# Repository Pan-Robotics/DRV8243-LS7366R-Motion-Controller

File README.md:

# DRV8243-LS7366R-Motion-Controller
Motion Control PCB, integrating the DRV8243 motor driver and LS7366R encoder reader for feedback control of DC motors

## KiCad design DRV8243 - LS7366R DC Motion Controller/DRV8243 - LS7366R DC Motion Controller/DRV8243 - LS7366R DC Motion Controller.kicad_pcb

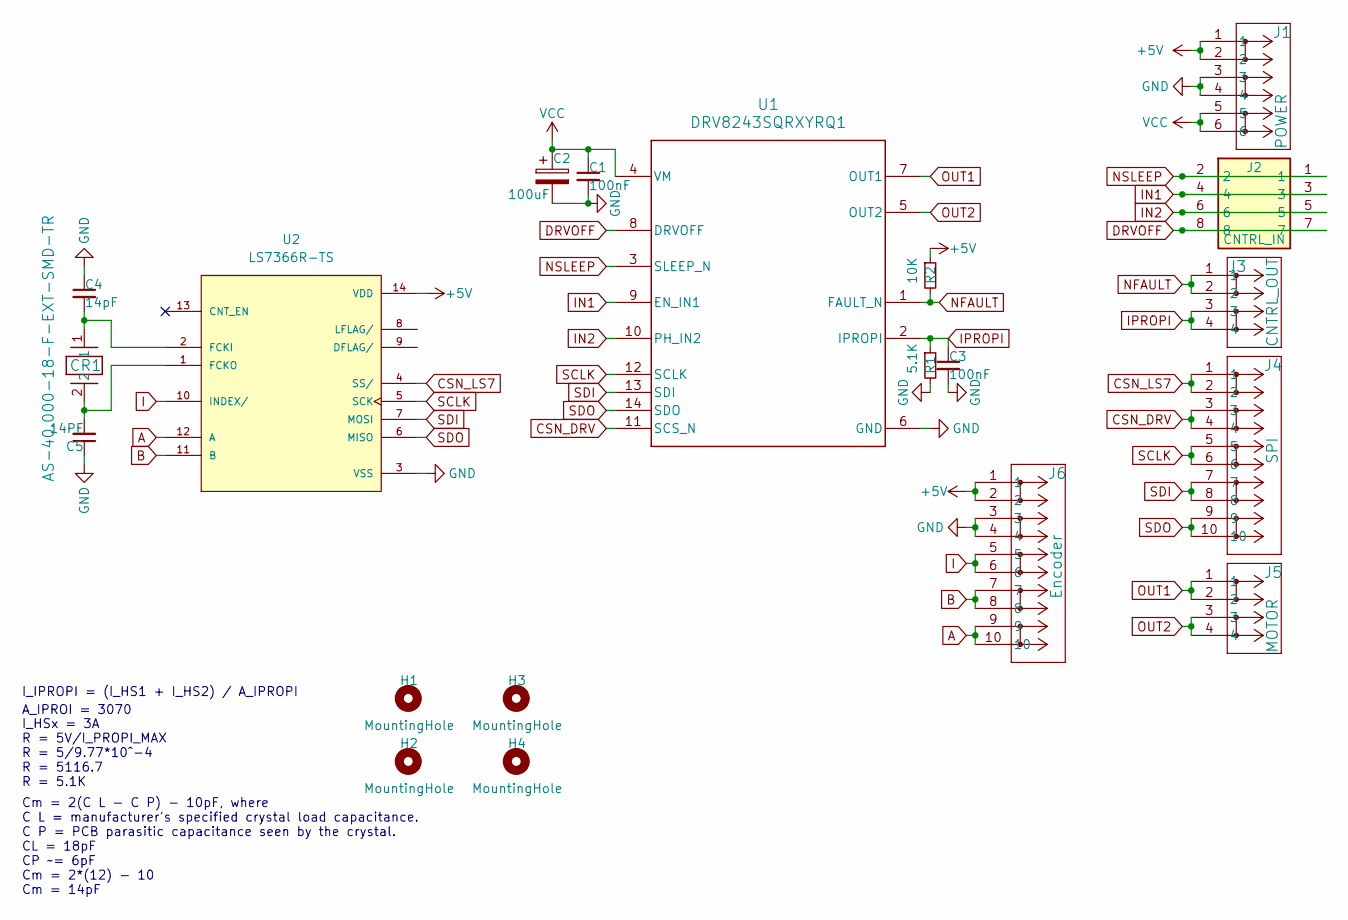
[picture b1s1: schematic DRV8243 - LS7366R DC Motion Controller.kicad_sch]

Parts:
C1, C3: 100nF; C_1206_3216Metric_Pad1.33x1.80mm_HandSolder
C2: 100uF; C_Elec_8x10.2
C4: 14pF; C_1206_3216Metric_Pad1.33x1.80mm_HandSolder
C5: 14PF; C_1206_3216Metric_Pad1.33x1.80mm_HandSolder
CR1: AS-40.000-18-F-EXT-SMD-TR; CRYSTAL_RAMI_HC-49&slash_S_STD_RAM
H1, H2, H3, H4: MountingHole; MountingHole_3.2mm_M3_Pad_Via
J1: POWER; CONN_1862055
J2: CNTRL_IN; 1862068; Mouser Part Number 651-1862068
J3: CNTRL_OUT; CONN_1862042
J4: SPI; CONN_1862071
J5: MOTOR; CONN_1862042
J6: Encoder; CONN_1862071
R1: 5.1K; R_1206_3216Metric_Pad1.30x1.75mm_HandSolder
R2: 10K; R_1206_3216Metric_Pad1.30x1.75mm_HandSolder
U1: DRV8243SQRXYRQ1; RXY0014A-MFG
U2: LS7366R-TS; SOP65P640X120-14N; PARTREV June 2014

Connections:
+5V: J1.1, J1.2, J6.1, J6.2, R2.1, U2.14 (VDD)
A: J6.9, J6.10, U2.12 (A)
B: J6.7, J6.8, U2.11 (B)
CSN_DRV: J4.3, J4.4, U1.11 (SCS_N)
CSN_LS7: J4.1, J4.2, U2.4 (SS/)
DRVOFF: J2.7, J2.8, U1.8 (DRVOFF)
GND: C1.2, C2.2, C3.2, C4.1, C5.1, J1.3, J1.4, J6.3, J6.4, R1.2, U1.6 (GND), U2.3 (VSS)
I: J6.5, J6.6, U2.10 (INDEX/)
IN1: J2.3, J2.4, U1.9 (EN_IN1)
IN2: J2.5, J2.6, U1.10 (PH_IN2)
IPROPI: C3.1, J3.3, J3.4, R1.1, U1.2 (IPROPI)
NFAULT: J3.1, J3.2, R2.2, U1.1 (FAULT_N)
NSLEEP: J2.1, J2.2, U1.3 (SLEEP_N)
unnamed: C4.2, CR1.1, U2.2 (FCKI)
unnamed: C5.2, CR1.2, U2.1 (FCKO)
OUT1: J5.1, J5.2, U1.7 (OUT1)
OUT2: J5.3, J5.4, U1.5 (OUT2)
SCLK: J4.5, J4.6, U1.12 (SCLK), U2.5 (SCK)
SDI: J4.7, J4.8, U1.13 (SDI), U2.7 (MOSI)
SDO: J4.9, J4.10, U1.14 (SDO), U2.6 (MISO)
VCC: C1.1, C2.1, J1.5, J1.6, U1.4 (VM)

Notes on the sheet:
I_HSx = 3A R = 5V/I_PROPI_MAX R = 5/9.77*10^-4 R = 5116.7 R = 5.1K
A_IPROI = 3070
Cm = 2(C L - C P) - 10pF, where C L = manufacturer's specified crystal load capacitance. C P = PCB parasitic capacitance seen by the crystal. CL = 18pF CP ~= 6pF Cm = 2*(12) - 10 Cm = 14pF
I_IPROPI = (I_HS1 + I_HS2) / A_IPROPI

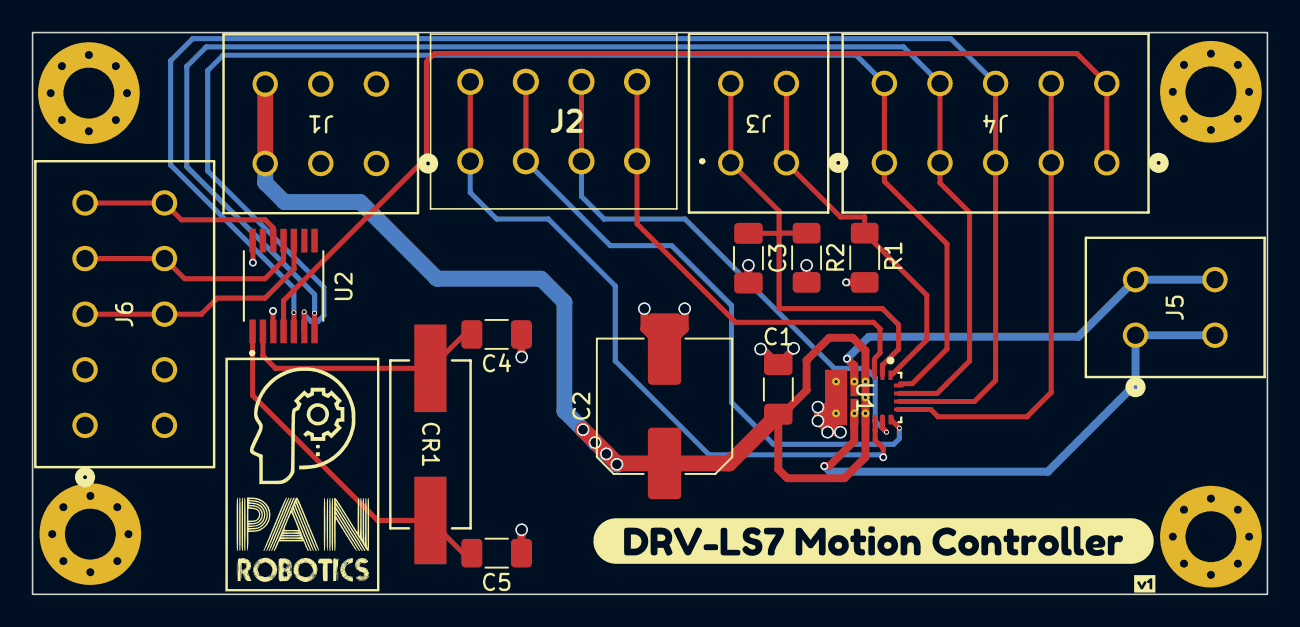
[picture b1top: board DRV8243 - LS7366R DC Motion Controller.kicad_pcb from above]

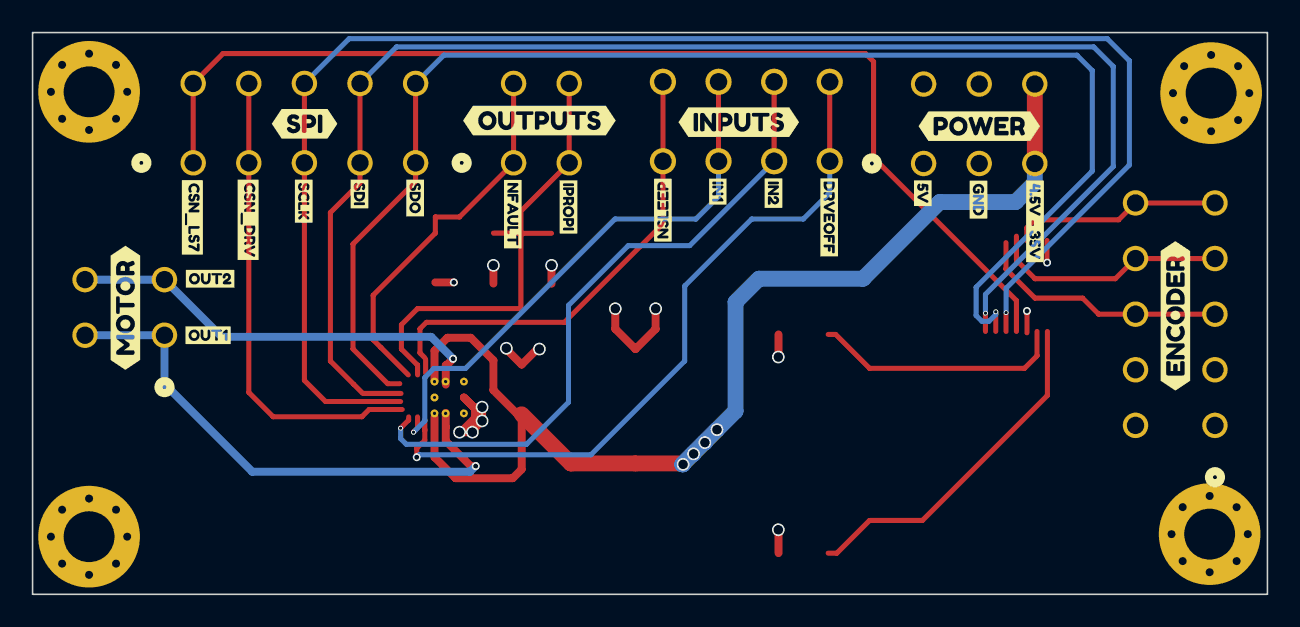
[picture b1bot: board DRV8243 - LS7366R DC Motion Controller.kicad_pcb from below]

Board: 4 copper layers, 77.7 x 35.4 mm, 44 parts (22 on the bottom side), 21 nets.

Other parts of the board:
kibuzzard-65A6FC0C: G***; kibuzzard-65A6FC0C
kibuzzard-65A6FCAC: G***; kibuzzard-65A6FCAC
kibuzzard-65A6FCCE: G***; kibuzzard-65A6FCCE
kibuzzard-65A6FCD9: G***; kibuzzard-65A6FCD9
kibuzzard-65A6FCE2: G***; kibuzzard-65A6FCE2
kibuzzard-65A6FD3E: G***; kibuzzard-65A6FD3E
kibuzzard-65A6FD04: G***; kibuzzard-65A6FD04
kibuzzard-65A6FD36: G***; kibuzzard-65A6FD36
kibuzzard-65A6FFF9: G***; kibuzzard-65A6FFF9
kibuzzard-65A7000E: G***; kibuzzard-65A7000E
kibuzzard-65A7001B: G***; kibuzzard-65A7001B
kibuzzard-65A7039D: G***; kibuzzard-65A7039D
kibuzzard-65A70003: G***; kibuzzard-65A70003
kibuzzard-65BE5B8E: G***; kibuzzard-65BE5B8E
kibuzzard-65BE5B66: G***; kibuzzard-65BE5B66
kibuzzard-65BE5BEC: G***; kibuzzard-65BE5BEC
kibuzzard-65BE5BF3: G***; kibuzzard-65BE5BF3
kibuzzard-65BE5BFB: G***; kibuzzard-65BE5BFB
kibuzzard-65BE5C3B: G***; kibuzzard-65BE5C3B
kibuzzard-65C4F8D9: G***; kibuzzard-65C4F8D9
kibuzzard-65C4F8EC: G***; kibuzzard-65C4F8EC
kibuzzard-65C4F282: G***; kibuzzard-65C4F282
kibuzzard-65C4F368: G***; kibuzzard-65C4F368
kibuzzard-65C504A9: G***; kibuzzard-65C504A9
